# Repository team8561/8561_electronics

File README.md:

# 8561_electronics
This repository contains the PCB and electrical files for FRC team 8561 Cartesian Robotics. All PCB's are designed in EAGLE cad.

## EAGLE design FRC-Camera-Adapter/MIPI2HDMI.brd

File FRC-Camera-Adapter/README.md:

IMPORTANT: We could not get the boards to function properly during the build season; therefore, we don't recommend that you make these boards yourselves.

This is the camera adapter board made by the electronics department of FRC Team 8561 during the 2025 season. The board's purpose is to carry MIPI CSI signals from our cameras to our coprocessor. Since there are numerous sources of interference within our robot, we decided against using standard ribbon cables, instead using HDMI cables, which provide the same differential impedance while also being shielded and more impact-resistant. The board includes ESD protection as well as overcurrent protection.

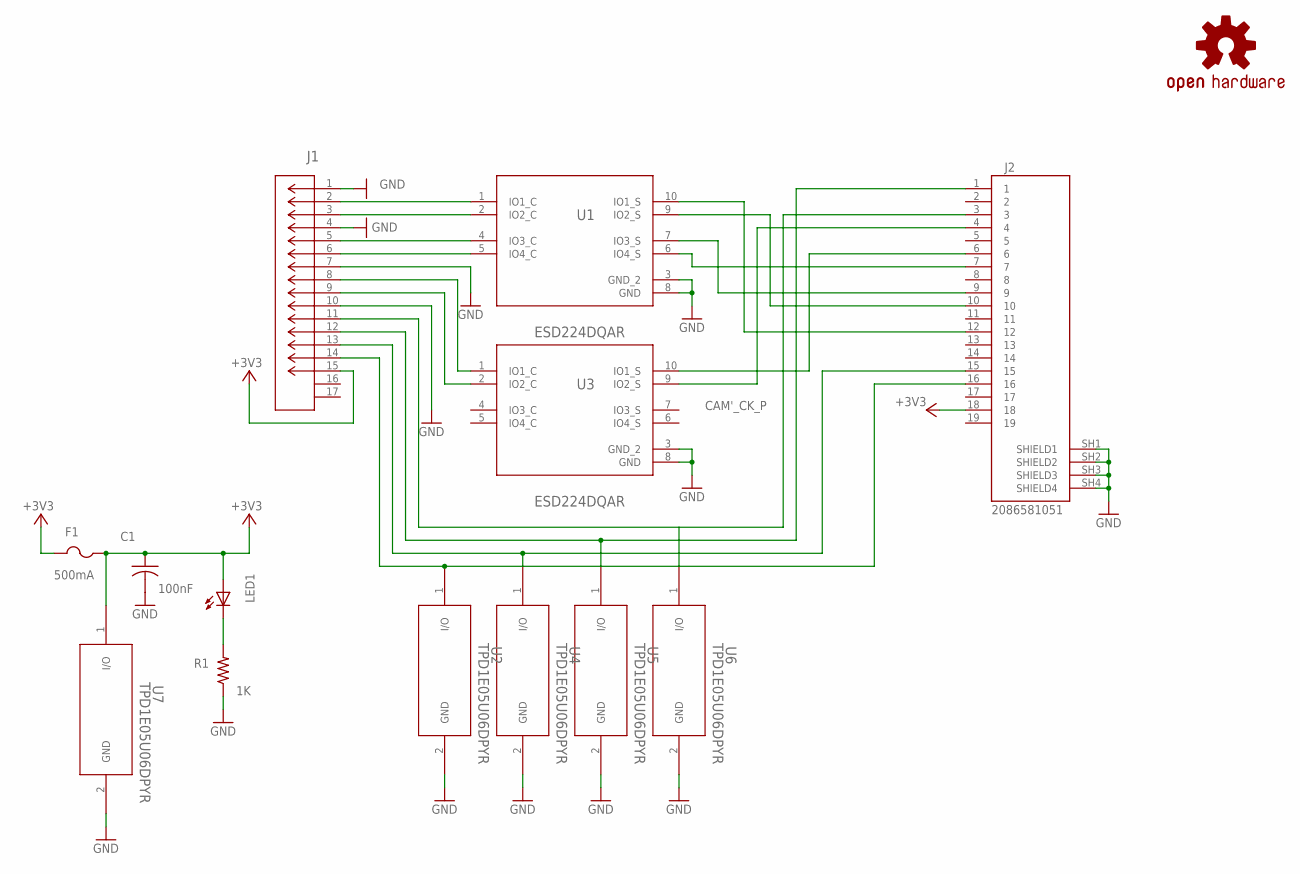
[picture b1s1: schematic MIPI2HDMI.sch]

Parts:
C1: 100nF; C0603
F1: 500mA; R1206
J1: 1-84952-5; CONN15_1-84952-5_TEC
J2: 2086581051; MOLEX_2086581051
LED1: LEDCHIP-LED0603; CHIP-LED0603
LOGO1: OSHW-LOGOM; OSHW-LOGO-M
R1: 1K; R0603
U1, U3: ESD224DQAR; DQA0010A
U2, U4, U5, U6, U7: TPD1E05U06DPYR; DPY2_TEX

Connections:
+3V3: C1.1, F1.1, F1.2, J1.15, J2.18, LED1.A, U7.1 (I/O)
CAM'_CK_N: J2.6, U3.10 (IO1_S)
CAM'_CK_P: J2.4, U3.9 (IO2_S)
CAM'_D0_N: J2.12, U1.10 (IO1_S)
CAM'_D0_P: J2.10, U1.9 (IO2_S)
CAM'_D1_N: J2.9, U1.7 (IO3_S)
CAM'_D1_P: J2.7, U1.6 (IO4_S)
CAM_CK_N: J1.8, U3.1 (IO1_C)
CAM_CK_P: J1.9, U3.2 (IO2_C)
CAM_D0_N: J1.2, U1.1 (IO1_C)
CAM_D0_P: J1.3, U1.2 (IO2_C)
CAM_D1_N: J1.5, U1.4 (IO3_C)
CAM_D1_P: J1.6, U1.5 (IO4_C)
CAM_MCLK: J1.12, J2.1, U5.1 (I/O)
CAM_SCL: J1.13, J2.15, U4.1 (I/O)
CAM_SDA: J1.14, J2.16, U2.1 (I/O)
GND: C1.2, J1.1, J1.4, J1.7, J1.10, J2.SH1 (SHIELD1), J2.SH2 (SHIELD2), J2.SH3 (SHIELD3), J2.SH4 (SHIELD4), R1.1, U1.3 (GND_2), U1.8 (GND), U2.2 (GND), U3.3 (GND_2), U3.8 (GND), U4.2 (GND), U5.2 (GND), U6.2 (GND), U7.2 (GND)
unnamed: LED1.C, R1.2
PWR_DN_LS: J1.11, J2.3, U6.1 (I/O)

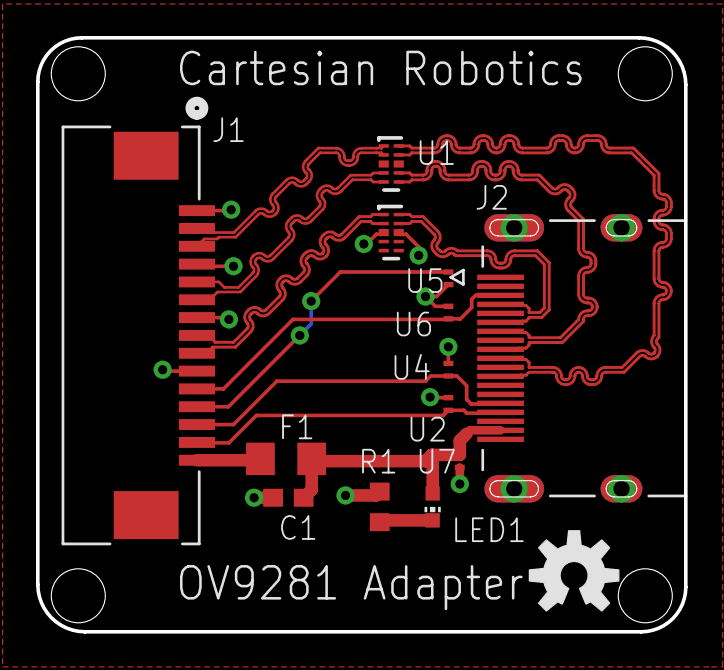
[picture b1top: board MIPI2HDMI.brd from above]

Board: 4 copper layers, 36.0 x 33.0 mm, 14 parts (0 on the bottom side), 19 nets.

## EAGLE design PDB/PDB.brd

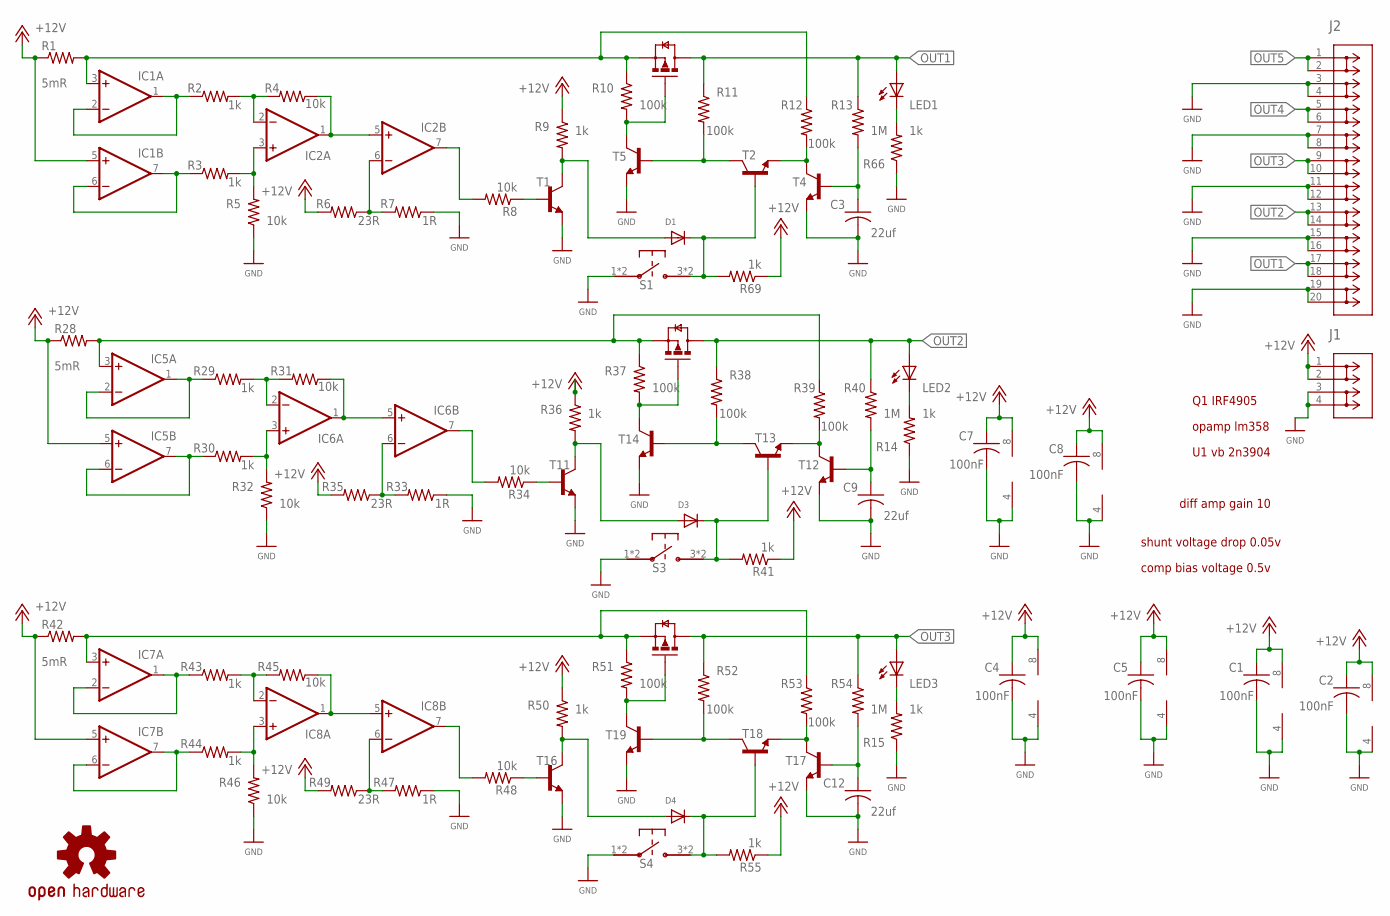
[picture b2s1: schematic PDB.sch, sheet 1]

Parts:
C1, C2, C4, C5, C7, C8: 100nF; C0603
C3, C9, C12: 22uf; C0805
D1, D3, D4: DIODESOD-323F; SOD-323F
IC1, IC2, IC5, IC6, IC7, IC8: LM358D; SO08
J1: 2606-1102; CONN2_2606-1102_WAG
J2: 2604-1110; CONN10_2604-1110_WAG
LED1, LED2, LED3: LEDCHIP-LED0603; CHIP-LED0603
LOGO1: OSHW-LOGOL; OSHW-LOGO-L
R1, R28, R42: 5mR; R2512
R2, R3, R9, R14, R15, R29, R30, R36, R41, R43, R44, R50, R55, R66, R69: 1k; R0603
R4, R5, R8, R31, R32, R34, R45, R46, R48: 10k; R0603
R6, R35, R49: 23R; R0603
R7, R33, R47: 1R; R0603
R10, R11, R12, R37, R38, R39, R51, R52, R53: 100k; R0603
R13, R40, R54: 1M; R0603
S1, S3, S4: PTS645SM43SMTR
T1, T2, T4, T5, T11, T12, T13, T14, T16, T17, T18, T19: 2N3904SMD; SOT23-BACKUP
T3, T15, T20: IRF4905; TO263-3

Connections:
+12V: C1.1, C2.1, C4.1, C5.1, C7.1, C8.1, IC1.5 (+IN), IC1.8 (V+), IC2.8 (V+), IC5.5 (+IN), IC5.8 (V+), IC6.8 (V+), IC7.5 (+IN), IC7.8 (V+), IC8.8 (V+), J1.1 (1_1), J1.2 (1_2), R1.1, R6.2, R9.1, R28.1, R35.2, R36.1, R41.1, R42.1, R49.2, R50.1, R55.1, R69.1; also elsewhere on the board
GND: C1.2, C2.2, C3.2, C4.2, C5.2, C7.2, C8.2, C9.2, C12.2, IC1.4 (V-), IC2.4 (V-), IC5.4 (V-), IC6.4 (V-), IC7.4 (V-), IC8.4 (V-), J1.3 (2_1), J1.4 (2_2), J2.3 (2_1), J2.4 (2_2), J2.7 (4_1), J2.8 (4_2), J2.11 (6_1), J2.12 (6_2), J2.15 (8_1), J2.16 (8_2), J2.19 (10_1), J2.20 (10_2), R5.1, R7.1, R14.1, R15.1, R32.1, R33.1, R46.1, R47.1, R66.1, S1.1, S1.2, S3.1, S3.2, S4.1, S4.2, T1.2 (E), T4.2 (E), T5.2 (E), T11.2 (E), T12.2 (E), T14.2 (E), T16.2 (E), T17.2 (E), T19.2 (E); also elsewhere on the board
N53: IC5.3 (+IN), R28.2, R37.1, R39.1, T15.3 (S)
unnamed: LED2.C, R14.2
unnamed: IC1.1 (OUT), IC1.2 (-IN), R2.1
unnamed: IC1.6 (-IN), IC1.7 (OUT), R3.1
unnamed: IC2.1 (OUT), IC2.5 (+IN), R4.1
unnamed: R8.1, T1.1 (B)
unnamed: IC2.7 (OUT), R8.2
unnamed: IC2.6 (-IN), R6.1, R7.2
unnamed: IC2.3 (+IN), R3.2, R5.2
unnamed: IC2.2 (-IN), R2.2, R4.2
unnamed: LED3.C, R15.2
unnamed: IC1.3 (+IN), R1.2, R10.1, R12.1, T3.3 (S)
unnamed: R10.2, T3.1 (G), T5.3 (C)
unnamed: R11.2, T2.3 (C), T5.1 (B)
unnamed: C3.1, R13.2, T4.1 (B)
unnamed: R12.2, T2.2 (E), T4.3 (C)
unnamed: LED1.C, R66.2
unnamed: IC5.1 (OUT), IC5.2 (-IN), R29.1
unnamed: IC5.6 (-IN), IC5.7 (OUT), R30.1
unnamed: IC6.6 (-IN), R33.2, R35.1
unnamed: IC6.3 (+IN), R30.2, R32.2
unnamed: IC6.2 (-IN), R29.2, R31.2
unnamed: IC6.1 (OUT), IC6.5 (+IN), R31.1
unnamed: R34.1, T11.1 (B)
unnamed: IC6.7 (OUT), R34.2
unnamed: R37.2, T14.3 (C), T15.1 (G)
unnamed: R38.2, T13.3 (C), T14.1 (B)
unnamed: C9.1, R40.2, T12.1 (B)
unnamed: R39.2, T12.3 (C), T13.2 (E)
unnamed: D3.C, R41.2, S3.3, S3.4, T13.1 (B)
unnamed: D3.A, R36.2, T11.3 (C)
unnamed: IC7.1 (OUT), IC7.2 (-IN), R43.1
unnamed: IC7.6 (-IN), IC7.7 (OUT), R44.1
unnamed: IC8.6 (-IN), R47.2, R49.1
unnamed: IC8.3 (+IN), R44.2, R46.2
unnamed: IC8.2 (-IN), R43.2, R45.2
unnamed: IC8.1 (OUT), IC8.5 (+IN), R45.1
unnamed: R48.1, T16.1 (B)
unnamed: IC8.7 (OUT), R48.2
unnamed: IC7.3 (+IN), R42.2, R51.1, R53.1, T20.3 (S)
unnamed: R51.2, T19.3 (C), T20.1 (G)
unnamed: R52.2, T18.3 (C), T19.1 (B)
unnamed: C12.1, R54.2, T17.1 (B)
unnamed: R53.2, T17.3 (C), T18.2 (E)
unnamed: D4.C, R55.2, S4.3, S4.4, T18.1 (B)
unnamed: D4.A, R50.2, T16.3 (C)
unnamed: D1.C, R69.2, S1.3, S1.4, T2.1 (B)
unnamed: D1.A, R9.2, T1.3 (C)
OUT1: J2.17 (9_1), J2.18 (9_2), LED1.A, R11.1, R13.1, T3.4 (D)
OUT2: J2.13 (7_1), J2.14 (7_2), LED2.A, R38.1, R40.1, T15.4 (D)
OUT3: J2.9 (5_1), J2.10 (5_2), LED3.A, R52.1, R54.1, T20.4 (D)
OUT4: J2.5 (3_1), J2.6 (3_2); also elsewhere on the board
OUT5: J2.1 (1_1), J2.2 (1_2); also elsewhere on the board

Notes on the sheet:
diff amp gain 10
shunt voltage drop 0.05v
comp bias voltage 0.5v
Q1 IRF4905
opamp lm358
U1 vb 2n3904

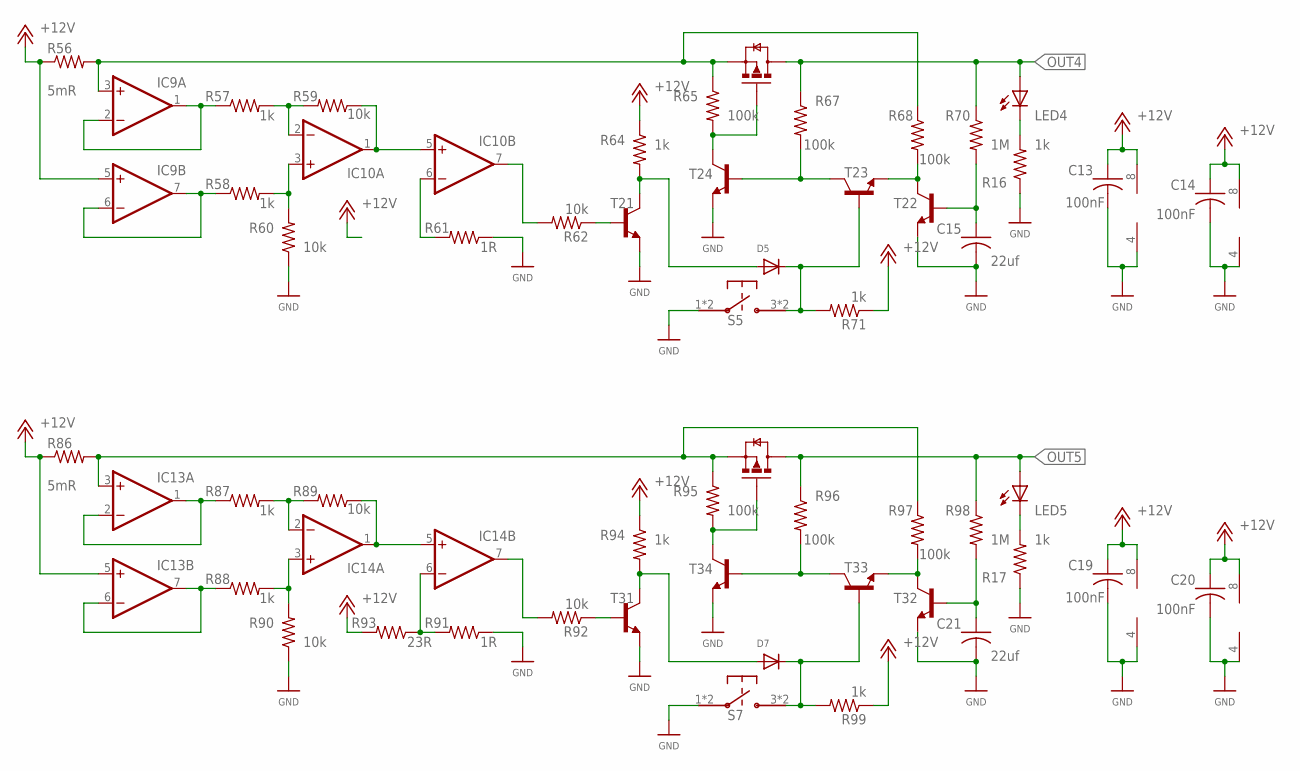
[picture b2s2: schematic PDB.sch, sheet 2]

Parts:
C13, C14, C19, C20: 100nF; C0603
C15, C21: 22uf; C0805
D5, D7: DIODESOD-323F; SOD-323F
IC9, IC10, IC13, IC14: LM358D; SO08
LED4, LED5: LEDCHIP-LED0603; CHIP-LED0603
R16, R17, R57, R58, R64, R71, R87, R88, R94, R99: 1k; R0603
R56, R86: 5mR; R2512
R59, R60, R62, R89, R90, R92: 10k; R0603
R61, R91: 1R; R0603
R65, R67, R68, R95, R96, R97: 100k; R0603
R70, R98: 1M; R0603
R93: 23R; R0603
S5, S7: PTS645SM43SMTR
T21, T22, T23, T24, T31, T32, T33, T34: 2N3904SMD; SOT23-BACKUP
T25, T35: IRF4905; TO263-3

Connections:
+12V: C13.1, C14.1, C19.1, C20.1, IC9.5 (+IN), IC9.8 (V+), IC10.8 (V+), IC13.5 (+IN), IC13.8 (V+), IC14.8 (V+), R56.1, R64.1, R71.1, R86.1, R93.2, R94.1, R99.1; also elsewhere on the board
GND: C13.2, C14.2, C15.2, C19.2, C20.2, C21.2, IC9.4 (V-), IC10.4 (V-), IC13.4 (V-), IC14.4 (V-), R16.1, R17.1, R60.1, R61.1, R90.1, R91.1, S5.1, S5.2, S7.1, S7.2, T21.2 (E), T22.2 (E), T24.2 (E), T31.2 (E), T32.2 (E), T34.2 (E); also elsewhere on the board
unnamed: LED4.C, R16.2
unnamed: LED5.C, R17.2
unnamed: IC9.1 (OUT), IC9.2 (-IN), R57.1
unnamed: IC9.6 (-IN), IC9.7 (OUT), R58.1
unnamed: IC10.6 (-IN), R61.2
unnamed: IC10.3 (+IN), R58.2, R60.2
unnamed: IC10.2 (-IN), R57.2, R59.2
unnamed: IC10.1 (OUT), IC10.5 (+IN), R59.1
unnamed: R62.1, T21.1 (B)
unnamed: IC10.7 (OUT), R62.2
unnamed: IC9.3 (+IN), R56.2, R65.1, R68.1, T25.3 (S)
unnamed: R65.2, T24.3 (C), T25.1 (G)
unnamed: R67.2, T23.3 (C), T24.1 (B)
unnamed: C15.1, R70.2, T22.1 (B)
unnamed: R68.2, T22.3 (C), T23.2 (E)
unnamed: D5.C, R71.2, S5.3, S5.4, T23.1 (B)
unnamed: D5.A, R64.2, T21.3 (C)
unnamed: IC13.1 (OUT), IC13.2 (-IN), R87.1
unnamed: IC13.6 (-IN), IC13.7 (OUT), R88.1
unnamed: IC14.6 (-IN), R91.2, R93.1
unnamed: IC14.3 (+IN), R88.2, R90.2
unnamed: IC14.2 (-IN), R87.2, R89.2
unnamed: IC14.1 (OUT), IC14.5 (+IN), R89.1
unnamed: R92.1, T31.1 (B)
unnamed: IC14.7 (OUT), R92.2
unnamed: IC13.3 (+IN), R86.2, R95.1, R97.1, T35.3 (S)
unnamed: R95.2, T34.3 (C), T35.1 (G)
unnamed: R96.2, T33.3 (C), T34.1 (B)
unnamed: C21.1, R98.2, T32.1 (B)
unnamed: R97.2, T32.3 (C), T33.2 (E)
unnamed: D7.C, R99.2, S7.3, S7.4, T33.1 (B)
unnamed: D7.A, R94.2, T31.3 (C)
OUT4: LED4.A, R67.1, R70.1, T25.4 (D); also elsewhere on the board
OUT5: LED5.A, R96.1, R98.1, T35.4 (D); also elsewhere on the board

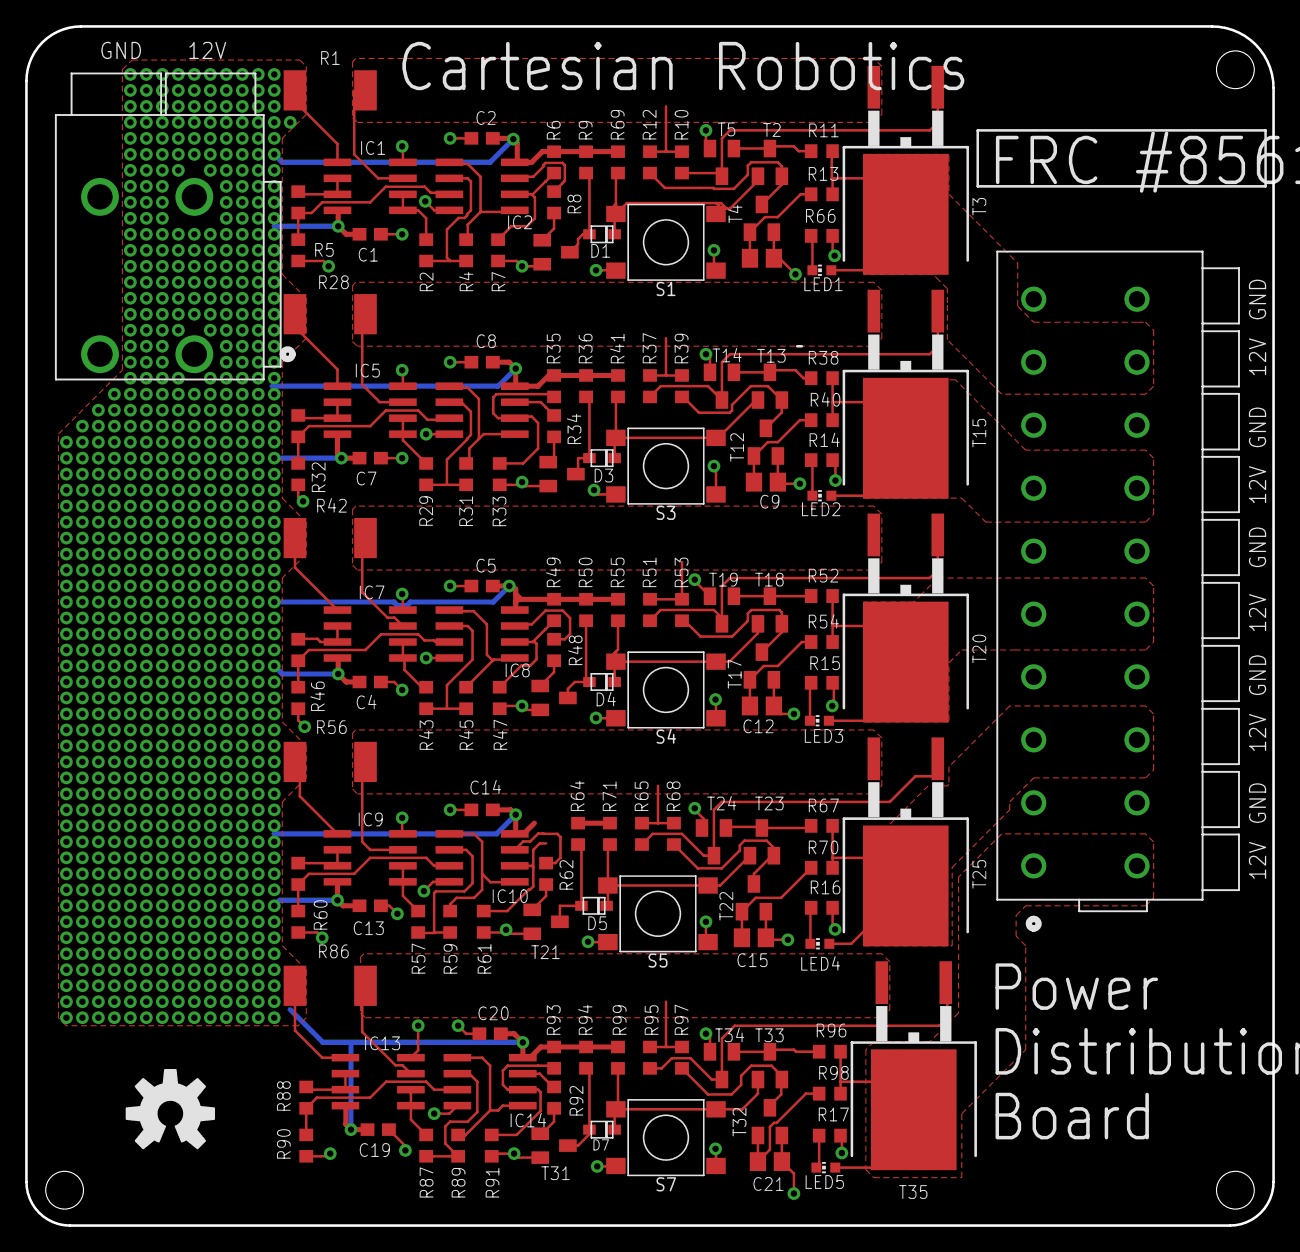
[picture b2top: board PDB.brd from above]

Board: 2 copper layers, 99.1 x 95.2 mm, 142 parts (0 on the bottom side), 87 nets.

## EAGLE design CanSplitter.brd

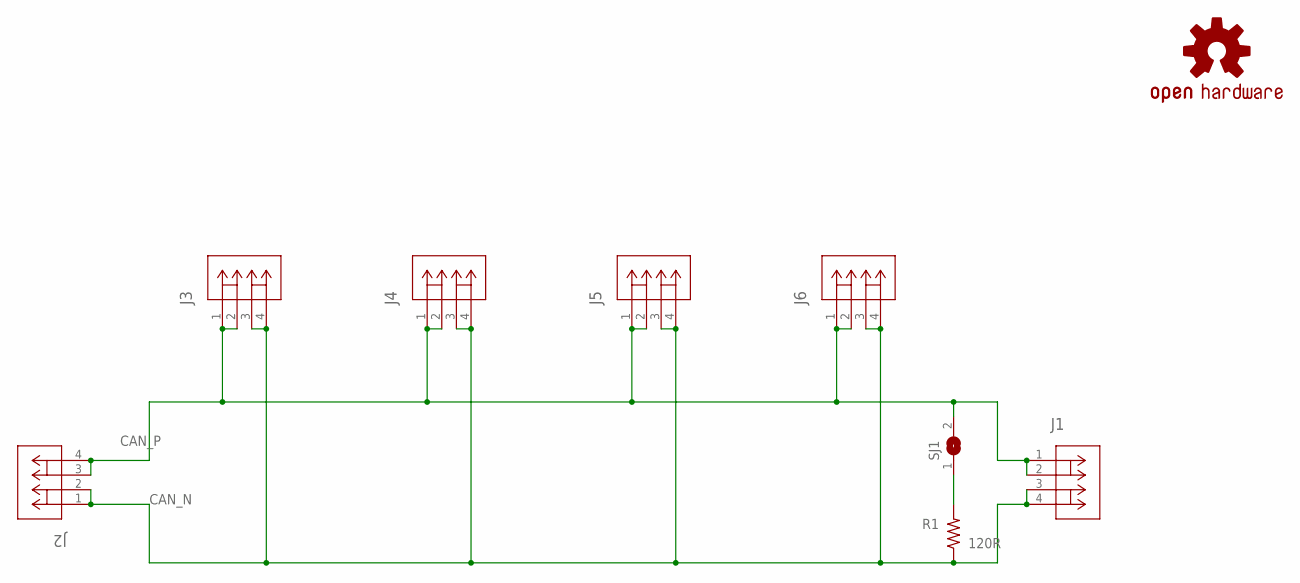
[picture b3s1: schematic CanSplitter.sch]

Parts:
J1, J2, J3, J4, J5, J6: 1885650000; CONN4_1885650000_WED
LOGO1: OSHW-LOGOL; OSHW-LOGO-L
R1: 120R; R0603
SJ1: SJ

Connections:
CAN_N: J1.3, J1.4, J2.1, J2.2, J3.3, J3.4, J4.3, J4.4, J5.3, J5.4, J6.3, J6.4, R1.1
CAN_P: J1.1, J1.2, J2.3, J2.4, J3.1, J3.2, J4.1, J4.2, J5.1, J5.2, J6.1, J6.2, SJ1.2
unnamed: R1.2, SJ1.1

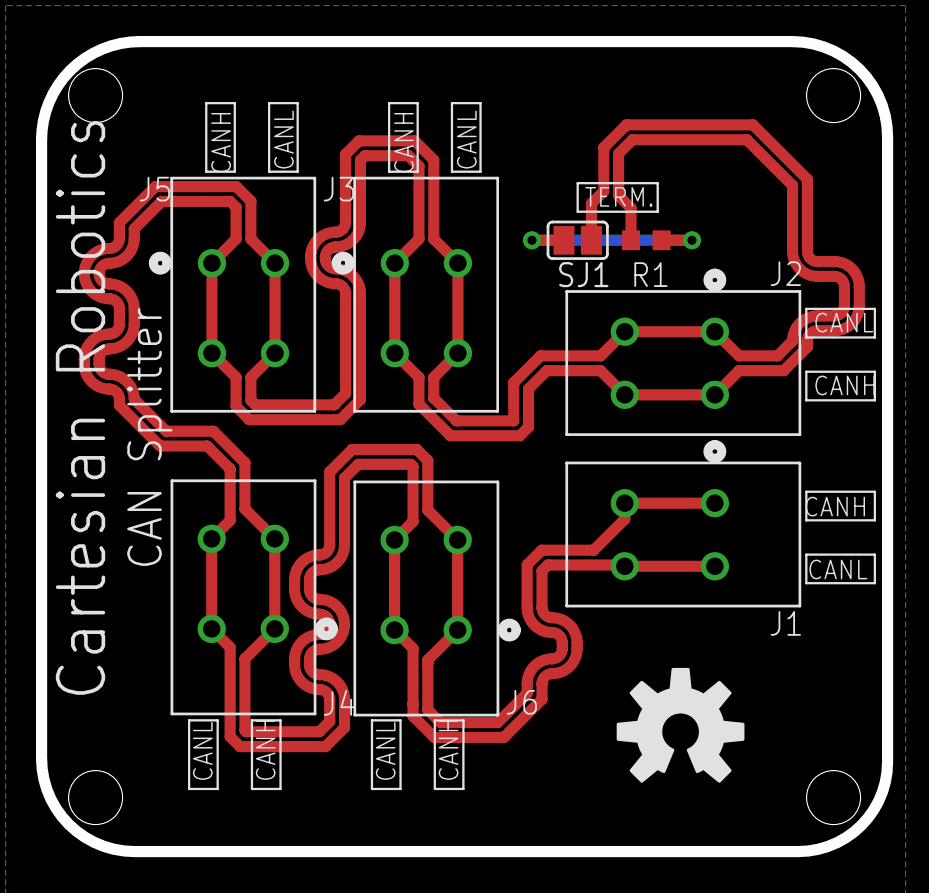
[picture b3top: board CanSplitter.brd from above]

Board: 2 copper layers, 47.0 x 45.0 mm, 9 parts (0 on the bottom side), 3 nets.

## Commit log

2025-01-08 Create CanSplitter
2025-01-09 Create placeholder
2025-05-01 Create FRC Camera Adapter

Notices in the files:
parts and their libraries:
SparkFun-Aesthetics: Licensing: Creative Commons ShareAlike 4.0 International - https://creativecommons.org/licenses/by-sa/4.0
COPYRIGHT: Copyright (C) 2025 Ultra Librarian. All rights reserved.
COPYRIGHT: Copyright (C) 2024 Ultra Librarian. All rights reserved.
